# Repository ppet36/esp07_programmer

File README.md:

# ESP8266-07 adapter for programming on 01 programmer

I created this adapter for programming and testing ESP07 on breadboard with cheap eBay ESP01 USB programmer. Is realized as single sided PCB with some wire jumpers.

There is nothing special. Inner sockets with 2mm pin distance is used to plug module (with soldered pins) and outer sockets with 2.54mm pin distance for wiring to breadboard. 2x4 pinstrip is soldered from bottom side of PCB.

## Some other project images

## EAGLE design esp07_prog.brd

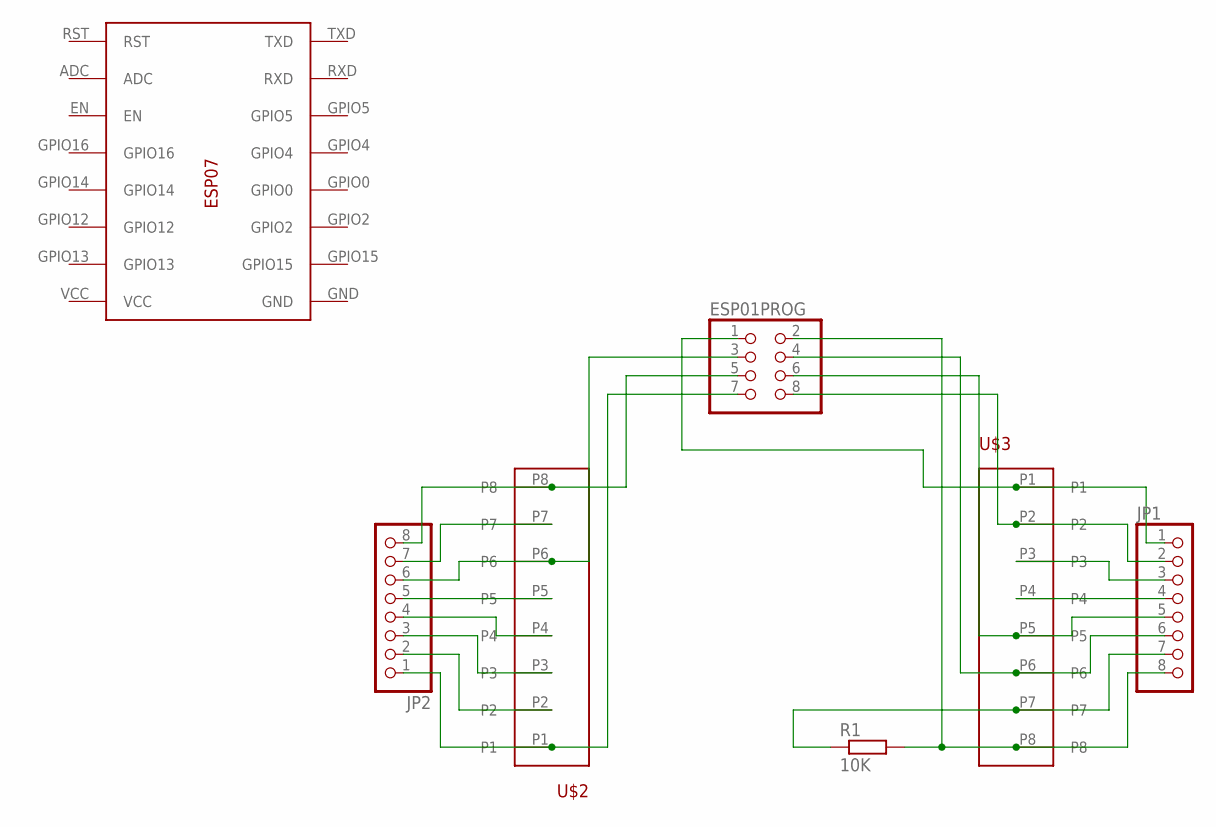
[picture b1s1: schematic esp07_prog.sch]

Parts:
ESP01PROG: PINHD-2X4; 2X04
JP1, JP2: PINHD-1X8; 1X08
R1: 10K; 0204/7
U$1: ESP07
U$2, U$3: PINHD8X2MM

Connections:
unnamed: ESP01PROG.5, JP2.8, U$2.P8
unnamed: JP2.7, U$2.P7
unnamed: ESP01PROG.3, JP2.6, U$2.P6
unnamed: JP2.5, U$2.P5
unnamed: JP2.4, U$2.P4
unnamed: JP2.3, U$2.P3
unnamed: JP2.2, U$2.P2
unnamed: ESP01PROG.7, JP2.1, U$2.P1
unnamed: ESP01PROG.1, JP1.1, U$3.P1
unnamed: ESP01PROG.8, JP1.2, U$3.P2
unnamed: JP1.3, U$3.P3
unnamed: JP1.4, U$3.P4
unnamed: ESP01PROG.6, JP1.5, U$3.P5
unnamed: ESP01PROG.4, JP1.6, U$3.P6
unnamed: ESP01PROG.2, JP1.8, R1.2, U$3.P8
unnamed: JP1.7, R1.1, U$3.P7

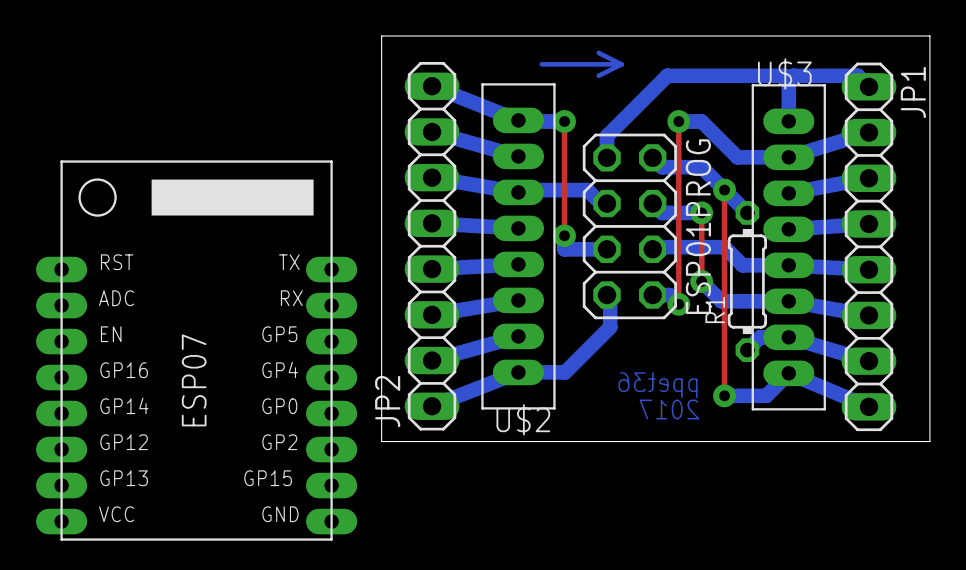
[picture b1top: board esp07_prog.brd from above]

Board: 2 copper layers, 30.5 x 22.5 mm, 7 parts (0 on the bottom side), 16 nets.

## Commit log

2017-01-17 Initial version
